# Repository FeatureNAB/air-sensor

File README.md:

# Smart E-Ink Air Quality Monitor
This repository contains all the 3D models, PCB production files, and ESPHome software configurations to build the Desktop Air Quality Monitor featured on [the channel](https://www.youtube.com/@FeatureNAB). 

The device uses an ESP32 and the Sensirion SEN66 to track 9 different air quality metrics (PM1, PM2.5, PM4, PM10, VOCs, NOx, CO2, Temperature, and Humidity) and displays them on an e-ink screen. It connects natively to [Home Assistant](https://www.home-assistant.io/) and the firmware is written using [ESPHome](https://esphome.io/).

3D Files can be found on [Printables](https://www.printables.com/model/1751003-smart-desktop-air-quality-monitor-esp32-sen66), on [Makerworld](https://makerworld.com/en/models/2918992-smart-desktop-air-quality-monitor-esp32-sen66), or in the releases tab.
  
## What's in this Repository?

**If you just want the final ready-to-go files, check the [Releases tab](../../releases) on the right!**

All source files are organized into their respective folders: 

*   📂 **`enclosure/`** - `.step` and `.3mf` models for the custom 3D printed housing.
*   📂 **`PCB/`** - Full KiCad project files and the `production` folder containing the Gerbers, BOM, and CPL files required for manufacturing.
*   📂 **`firmware/`** - ESPHome `.yaml` configuration files, plus precompiled bin files that you can flash directly to your board (Minimal and Home Assistant versions available).

## Getting Started

This project comes in 2 flavours - the minimal "just get the sensor working" variant, and the full variant that uses a custom PCB and a 3D printed housing.

### Minimal variant 

#### 1. Hardware
To build this version, you will need:

*   [Sensirion SEN66](https://mou.sr/44c63Ji)
*   [Seeed XIAO ESP32-C6](https://www.youtube.com/redirect?event=video_description&redir_token=QUFFLUhqbEVLbTd0dGJnZFpQeENEZVg1UGV1QXZnaUF5UXxBQ3Jtc0tuU0hGTnIzSEkyQ1NUTmktUU1jV1ZqeVBKUG5LbHlEQ3ZrbjM0MkF5VjBqczRQbVNVd1lCc0IwV2NaUm5vb1FXYU1ZSzBDdEpOTm85MUpHb0VqLWpDdVdZSXR3NWdzQ0hybEtKcmFlbVRkcVdJc2p5RQ&q=https%3A%2F%2Fwww.seeedstudio.com%2FSeeed-StudioXIAO-ESP32C6-3PCS-p-5918.html%3Fsensecap_affiliate%3DdzMqXsY%26referring_service%3Dlink&v=DqiMmY5ppnE) microcontroller
*   [A JST-GH to Dupont cable](https://www.tinytronics.nl/en/cables-and-connectors/cables-and-adapters/jst-compatible/jst-ghr-06v-s-to-dupont-female-compatible-cable-6p-15cm) to connect them

Assemble by connecting the 3V, GND, SDA and SCL pins as shown in the video.

#### 2. Firmware

**Method A: "As Fast As Possible" (No Coding Required)**
1. If you plan to use the device with Home Assistant, download `Firmware_minimal_with_Home_Assistant_bins.zip `, if you plan to use it standalone use `Firmware_minimal_air_sensor_bins.zip ` from the Releases tab on the right side of this page.
2. Plug your ESP32 (C3, C5, C6, or S3) into your computer via USB.
3. Using a Web Serial compatible browser (like Chrome or Edge), go to [web.esphome.io](https://web.esphome.io).
4. Click "Connect", select your board's COM port, and upload the `.bin` file that matches your specific ESP32 model.
5. Connect to the device's fallback Wi-Fi network to add it to your home network!

**Method B: Do this if you already have Home Assistant (or want to customise your setup)**
1. Open the `Software` folder and grab the relevant `.yaml` config file. Copy its contents.
2. Paste it into your ESPHome Builder dashboard.
3. Edit your Wi-Fi credentials, encryption keys, and anything else you want to try.
4. "Install" to compile and flash directly to your board.

---

### Full Variant
#### 1. Hardware
To build this version, you will need:

*   [Sensirion SEN66](https://mou.sr/44c63Ji)
*   [Seeed XIAO ESP32-C6](https://www.youtube.com/redirect?event=video_description&redir_token=QUFFLUhqbEVLbTd0dGJnZFpQeENEZVg1UGV1QXZnaUF5UXxBQ3Jtc0tuU0hGTnIzSEkyQ1NUTmktUU1jV1ZqeVBKUG5LbHlEQ3ZrbjM0MkF5VjBqczRQbVNVd1lCc0IwV2NaUm5vb1FXYU1ZSzBDdEpOTm85MUpHb0VqLWpDdVdZSXR3NWdzQ0hybEtKcmFlbVRkcVdJc2p5RQ&q=https%3A%2F%2Fwww.seeedstudio.com%2FSeeed-StudioXIAO-ESP32C6-3PCS-p-5918.html%3Fsensecap_affiliate%3DdzMqXsY%26referring_service%3Dlink&v=DqiMmY5ppnE) microcontroller
*   [2.13" e-ink Monochrome Display](https://www.seeedstudio.com/2-13-Monochrome-ePaper-Display-with-122x250-Pixels-p-5778.html?sensecap_affiliate=dzMqXsY&referring_service=link) (Note: this MUST be monochrome, the current PCB design DOES NOT WORK with colour epaper)
*   Custom epaper driver board PCB (see below)
*   4x M3 size heat set inserts. I used Ruthex.
*   4x M3 bolts for the front + 1x M3 bolt to keep the PCB in place in the enclosure. CNC Kitchen sell these.
*   A cable to connect the SEN66 to the board
    *  I used a stemma cable, cut it in half, and soldered it to a JST-GH 1.25mm pre-crimped cable.
    *  Alternatively if you will use the dupont headers on the board you can buy premade cables [like these](https://www.amazon.ie/Connectors-Pre-Crimped-Compatible-Pixhawk4-Silicone/dp/B0CLD7S5VC) (note this cable won't attach to the stemma convenience connector on the PCB!)   

#### 2. PCB
I designed the PCB to be manufactured and assembled by [JLCPCB](https://jlcpcb.com/?from=FEATURE). The ordering process is shown in the video. JLCPCB also offer 3D Printing Services through JLC3DP, so you could have the enclosure made too if you dont have a 3D printer, and they also offer CNC machining services through JLCCNC, if you wanted to make one from metals for a super unique finish.
1. Head to the **[Releases tab](../../releases)** and download the `PCB_fabrication_files.zip `.
2. Upload the Gerber zip to JCLPCB.
3. Enable **PCBA** (PCB Assembly) to have the tiny SMD components soldered for you.
4. Upload the BOM and positions from the zip file.
5. Order and wait for the goods to arrive.

#### 3. 3D Printing the Enclosure
Download the `3D_Files.zip` from the Releases tab and print the enclosure. 
*   The `.3mf` file is pre-configured and ready to print.
*   The `.step` file is provided if you want to modify the housing in any way. 

#### 4. Firmware
Same method as the Method B: firmware steps above. The yaml, images, and extra code for the display and air algorithm is provided for you in the `firmware/The Everything Bagel` folder, but you'll need to compile it yourself in ESPHome Builder or the ESPHome CLI. 

## Home Assistant Dashboard

If you are connecting this to Home Assistant and want the UI dashboard card shown in the video, you will need to install HACS (Home Assistant Community Store) and download the **[Air Quality Card by KadenThomp36](https://github.com/KadenThomp36/air-quality-card)**. The thresholds and algorithms in my `aqi_algo.h` match the WHO 2021 recommendations also used by this card, so the recommendations shown on the physical display on this Air Quality device should match those on this card/dashboard.

## Support the project
[Patreon](https://www.patreon.com/FEATURE418) for anyone interested, so I can continue making projects like this. Thanks!

Some of the links on this page are affiliate links and help support these projects at no cost to you.

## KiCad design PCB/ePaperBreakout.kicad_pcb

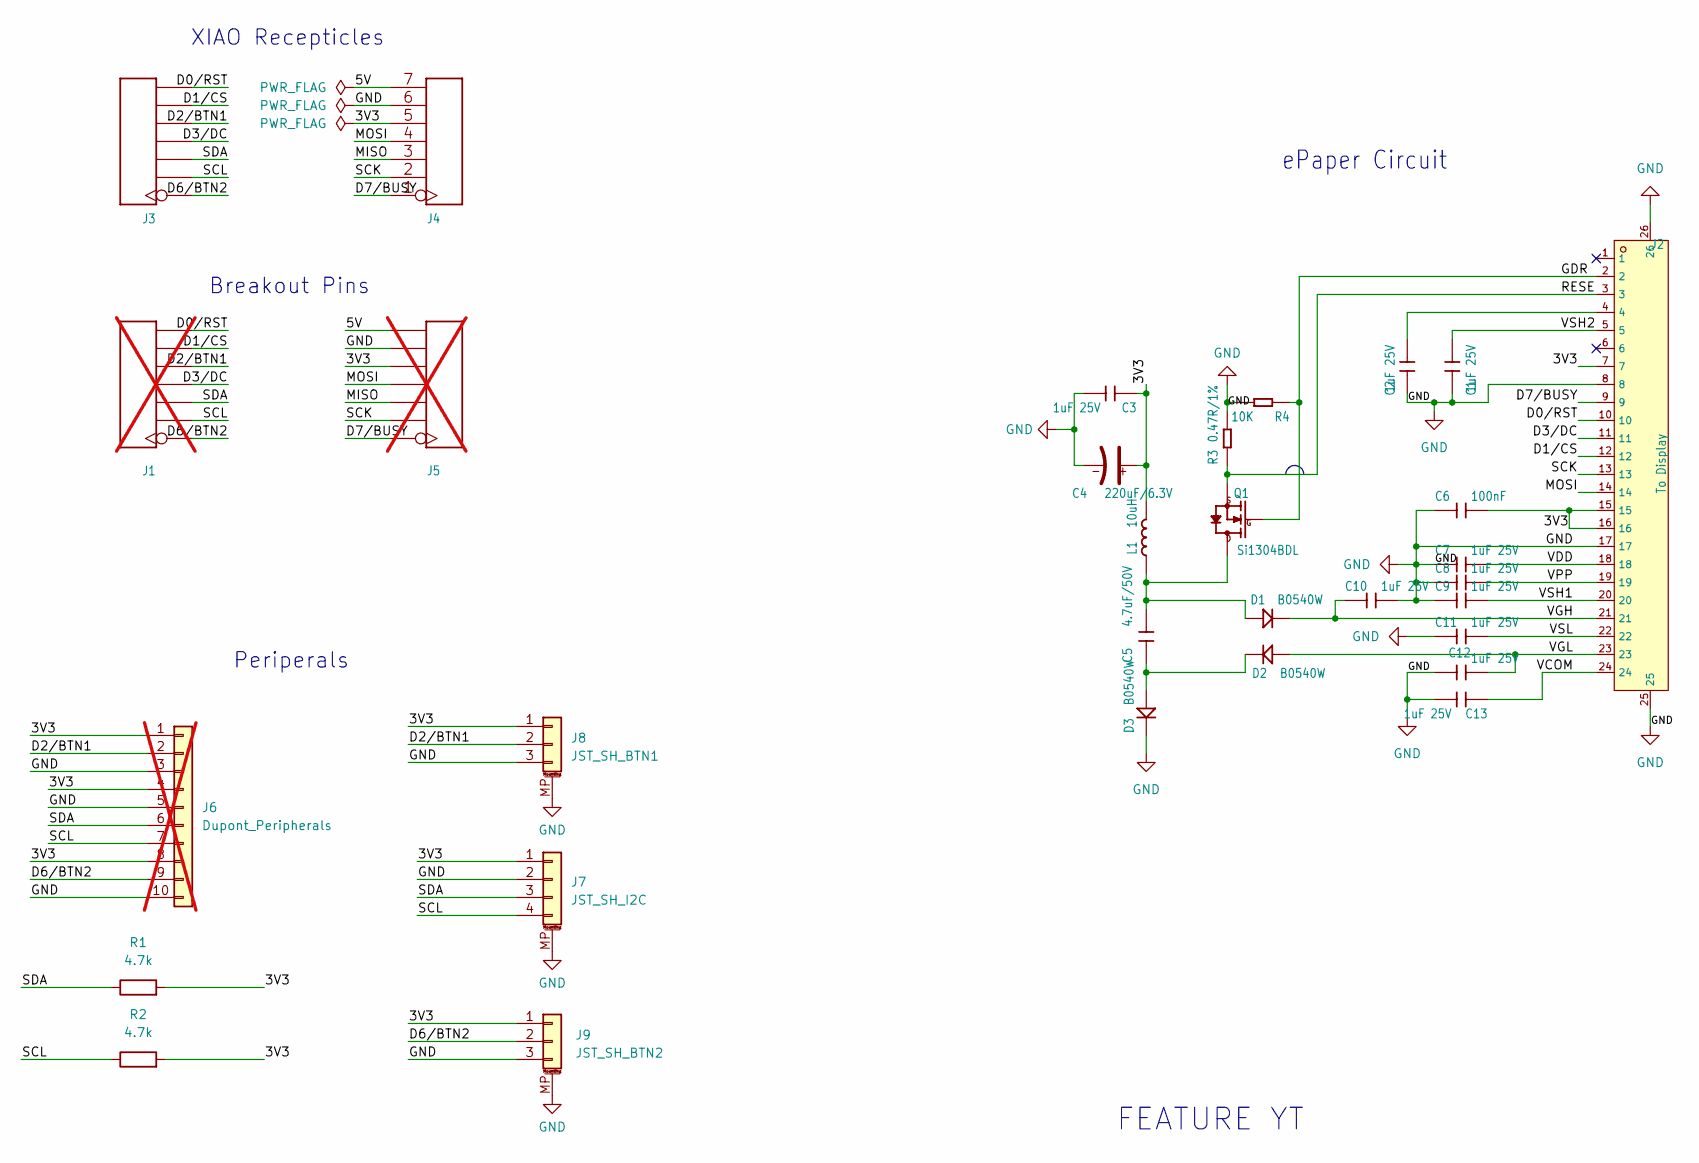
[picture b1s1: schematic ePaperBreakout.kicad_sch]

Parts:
C1, C2, C3, C7, C8, C9, C10, C11, C12, C13: 1uF 25V; C_0603_1608Metric; LCSC Part no. C96446
C4: 220uF/6.3V; CP_EIA-3528-21_Kemet-B; LCSC Part no. C30242
C5: 4.7uF/50V; C_1206_3216Metric; LCSC Part no. C318753
C6: 100nF; C_0603_1608Metric; LCSC Part no. C5969204
D1, D2, D3: B0540W; D_SOD-123; LCSC Part no. C7420325
J1, J5: HEADER-8P-80/40MIL; PinHeader_1x07_P2.54mm_Vertical; not fitted
J2: To Display; FPC-SMD_24P-P0.50_XFCN_F0504-H-24-20T-R; LCSC Part no. C5200280
J3, J4: HEADER-7P-18.28X2.5; PinSocket_1x07_P2.54mm_Vertical_SMD_Pin1Right; LCSC Part no. C42379199
J6: Dupont_Peripherals; PinHeader_1x10_P2.54mm_Horizontal; not fitted
J7: JST_SH_I2C; JST_SH_SM04B-SRSS-TB_1x04-1MP_P1.00mm_Horizontal; LCSC Part no. C160404
J8: JST_SH_BTN1; JST_SH_SM03B-SRSS-TB_1x03-1MP_P1.00mm_Horizontal; LCSC Part no. C160403
J9: JST_SH_BTN2; JST_SH_SM03B-SRSS-TB_1x03-1MP_P1.00mm_Horizontal; LCSC Part no. C160403
L1: 10uH; IND-SMD_L5.2-W5.2_MCW-0530; LCSC Part no. C181721
Q1: Si1304BDL; SOT-323_SC-70; LCSC Part no. C7419947
R1, R2: 4.7k; R_0402_1005Metric; LCSC Part no. C2907034
R3: 0.47R/1%; R_0603_1608Metric; LCSC Part no. C23411
R4: 10K; R_0603_1608Metric; LCSC Part no. C2906982

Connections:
/3V3: C3.1, C4.1 (+), C6.2, J2.7, J2.15, J2.16, J4.5, J5.5, J6.1, J6.4, J6.8, J7.1, J8.1, J9.1, L1.2, R1.2, R2.2; also elsewhere on the board
/5V: J4.7, J5.7
/D0/RST: J1.7, J2.10, J3.7
/D1/CS: J1.6, J2.12, J3.6
/D2/BTN1: J1.5, J3.5, J6.2, J8.2
/D3/DC: J1.4, J2.11, J3.4
/D6/BTN2: J1.1, J3.1, J6.9, J9.2
/D7/BUSY: J2.9, J4.1, J5.1
/GDR: J2.2, Q1.1 (G), R4.1
/MISO: J4.3, J5.3
/MOSI: J2.14, J4.4, J5.4
/RESE: J2.3, Q1.2 (S), R3.1
/SCK: J2.13, J4.2, J5.2
/SCL: J1.2, J3.2, J6.7, J7.4, R2.1; also elsewhere on the board
/SDA: J1.3, J3.3, J6.6, J7.3, R1.1; also elsewhere on the board
/VCOM: C13.1, J2.24
/VDD: C7.2, J2.18
/VGH: C10.1, D1.1 (-), J2.21
/VGL: C12.2, D2.2 (+), J2.23
/VPP: C8.2, J2.19
/VSH1: C9.2, J2.20
/VSH2: C1.1, J2.5
/VSL: C11.2, J2.22
GND: C1.2, C2.2, C3.2, C4.2 (-), C6.1, C7.1, C8.1, C9.1, C10.2, C11.1, C12.1, C13.2, D3.1 (-), J2.8, J2.17, J2.25, J2.26, J4.6, J5.6, J6.3, J6.5, J6.10, J7.2, J7.MP (MountPin), J8.3, J8.MP (MountPin), J9.3, J9.MP (MountPin), R3.2, R4.2; also elsewhere on the board
unnamed: C2.1, J2.4
unnamed: C5.2, D1.2 (+), L1.1, Q1.3 (D)
unnamed: C5.1, D2.1 (-), D3.2 (+)

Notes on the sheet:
ePaper Circuit
Breakout Pins
FEATURE YT
Periperals
XIAO Recepticles

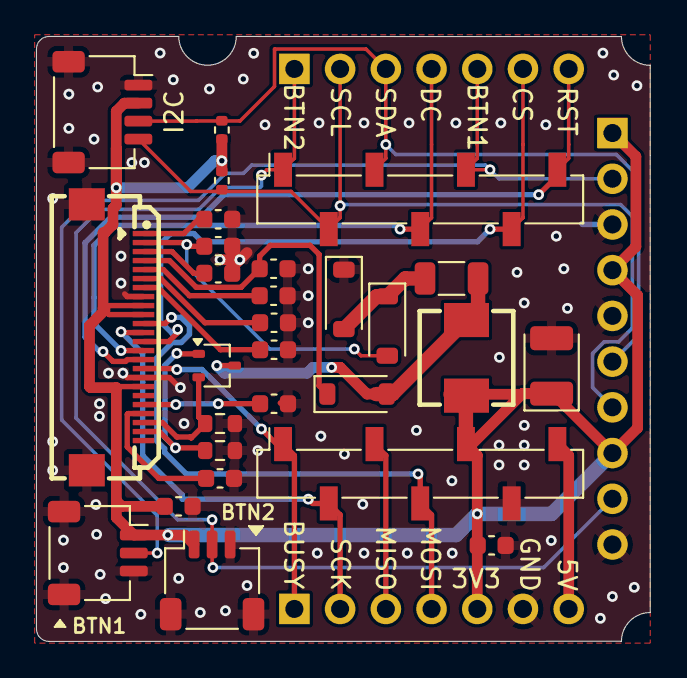
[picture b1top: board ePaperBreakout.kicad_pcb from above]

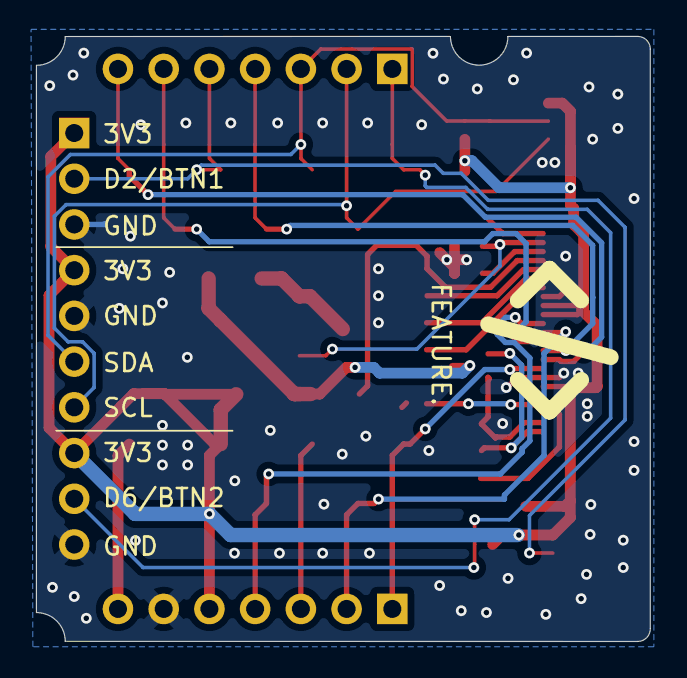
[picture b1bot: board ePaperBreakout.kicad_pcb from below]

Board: 2 copper layers, 34.1 x 33.6 mm, 31 parts (3 on the bottom side), 27 nets.

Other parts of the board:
I2C: JST_SH_I2C; JST_SH_SM04B-SRSS-TB_1x04-1MP_P1.00mm_Horizontal

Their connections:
/3V3: I2C.2; also elsewhere on the board
/SCL: I2C.4; also elsewhere on the board
/SDA: I2C.3; also elsewhere on the board
GND: I2C.1, I2C.MP (MountPin); also elsewhere on the board

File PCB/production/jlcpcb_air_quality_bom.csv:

"Reference","Qty","Value","DNP","Exclude from BOM","Exclude from Board","Footprint","Datasheet","LCSC Part no."
"C1,C2,C3,C7,C8,C9,C10,C11,C12,C13","10","1uF 25V","","","","Capacitor_SMD:C_0603_1608Metric","https://www.lcsc.com/product-detail/C96446.html","C96446"
"C4","1","220uF/6.3V","","","","Capacitor_Tantalum_SMD:CP_EIA-3528-21_Kemet-B","https://www.lcsc.com/product-detail/C30242.html","C30242"
"C5","1","4.7uF/50V","","","","Capacitor_SMD:C_1206_3216Metric","https://www.lcsc.com/product-detail/C318753.html","C318753"
"C6","1","100nF","","","","Capacitor_SMD:C_0603_1608Metric","https://www.lcsc.com/product-detail/C5969204.html","C5969204"
"D1,D2,D3","3","B0540W","","","","Diode_SMD:D_SOD-123","https://www.lcsc.com/product-detail/C7420325.html","C7420325"
"J1,J5","2","HEADER-8P-80/40MIL","DNP","","","Connector_PinHeader_2.54mm:PinHeader_1x07_P2.54mm_Vertical","",""
"J2","1","To Display","","","","RandomThings:FPC-SMD_24P-P0.50_XFCN_F0504-H-24-20T-R","https://www.lcsc.com/product-detail/C5200280.html","C5200280"
"J3,J4","2","HEADER-7P-18.28X2.5","","","","Connector_PinSocket_2.54mm:PinSocket_1x07_P2.54mm_Vertical_SMD_Pin1Right","https://www.lcsc.com/product-detail/C42379199.html","C42379199"
"J6","1","Dupont_Peripherals","DNP","","","Connector_PinHeader_2.54mm:PinHeader_1x10_P2.54mm_Horizontal","~",""
"J7","1","JST_SH_I2C","","","","Connector_JST:JST_SH_SM04B-SRSS-TB_1x04-1MP_P1.00mm_Horizontal","https://www.lcsc.com/product-detail/C160404.html","C160404"
"J8","1","JST_SH_BTN1","","","","Connector_JST:JST_SH_SM03B-SRSS-TB_1x03-1MP_P1.00mm_Horizontal","https://www.lcsc.com/product-detail/C160403.html","C160403"
"J9","1","JST_SH_BTN2","","","","Connector_JST:JST_SH_SM03B-SRSS-TB_1x03-1MP_P1.00mm_Horizontal","https://www.lcsc.com/product-detail/C160403.html","C160403"
"L1","1","10uH","","","","RandomThings:IND-SMD_L5.2-W5.2_MCW-0530","https://www.lcsc.com/product-detail/C181721.html","C181721"
"Q1","1","Si1304BDL","","","","Package_TO_SOT_SMD:SOT-323_SC-70","https://www.lcsc.com/product-detail/C7419947.html","C7419947"
"R1,R2","2","4.7k","","","","Resistor_SMD:R_0402_1005Metric","https://www.lcsc.com/product-detail/C2907034.html","C2907034"
"R3","1","0.47R/1%","","","","Resistor_SMD:R_0603_1608Metric","https://www.lcsc.com/product-detail/C23411.html","C23411"
"R4","1","10K","","","","Resistor_SMD:R_0603_1608Metric","https://www.lcsc.com/product-detail/C2906982.html","C2906982"

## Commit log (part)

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2026-06-11 Fix e-ink link
